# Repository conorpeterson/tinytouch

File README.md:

# TinyTouch
** Simple and reliable finger-to-PCB touch sensing **   
By Conor Peterson - conor.p.peterson@gmail.com 2016

License: Creative Commons Attribution-ShareAlike 4.0 International (CC BY-SA 4.0)

This project demonstrates simple and reliable on/off capacitive touch sensing. It is designed for use in interactive artworks or museum displays but would be well-suited for any hardwired application that requires oversized, physically accessible buttons located a distance from the controlling hardware.

The project is built around an ATtiny microcontroller so is compatible with 5v and 3.3v power supplies. The output of the detection unit is a clean high/low signal. Presses of variable duration are detected within reasonable limits.

The sensing element is built into the PCB itself and is designed to be directly touched by the user for maximum reliability. Material may be placed over the sensing element but should be kept thin, no thicker than typing paper (~.003" / .08mm). Certain materials may require adjustment of sensitivity threshold, or more substantial adaptations including the sensing element resistors (R3 and R4), the sampling interval or possibly the clock speed of the microcontroller.

One of the challenges in capacitive touch sensing is that the measurements tend to drift according to changes in temperature and humidity. This design attempts to address this by calibrating the detection floor at startup and at regular intervals thereafter. Consequently the sensor is best suited for momentary presses only - continuous contact for more than several seconds is to be avoided.

## Contents
### Firmware
This folder contains the source code for the ATtiny25/45/85 microcontroller. It has been tested to compile within a Linux environment using avr-gcc 4.9.2 and avr-libc 1.8.0. The bin subfolder contains pre-compiled hex files suitable for flashing with avrdude. NOTE: you must alter the fuse bits so that the chip runs at 8 MHz; this can be done by invoking the "fuses" target in the supplied makefile.

### Schematic
Contains a Kicad 4.x schematic for the project, plus a the reference PCB layout and fabrication-ready gerbers. The artwork in the TT_SMT_GRAPHICS subfolder can be modified and passed through Kicad's bitmap-to-component converter to create the custom touch sensor soldermask.

## License
The contents of this project are provided under the Creative Commons Attribution-ShareAlike 4.0 license.
(https://creativecommons.org/licenses/by-sa/4.0/legalcode)

You are free to:  
Share — copy and redistribute the material in any medium or format  
Adapt — remix, transform, and build upon the material for any purpose, even commercially.  
Under the following terms:  
Attribution — You must give appropriate credit, provide a link to the license, and indicate if changes were made. You may do so in any reasonable manner, but not in any way that suggests the licensor endorses you or your use.  
ShareAlike — If you remix, transform, or build upon the material, you must distribute your contributions under the same license as the original.

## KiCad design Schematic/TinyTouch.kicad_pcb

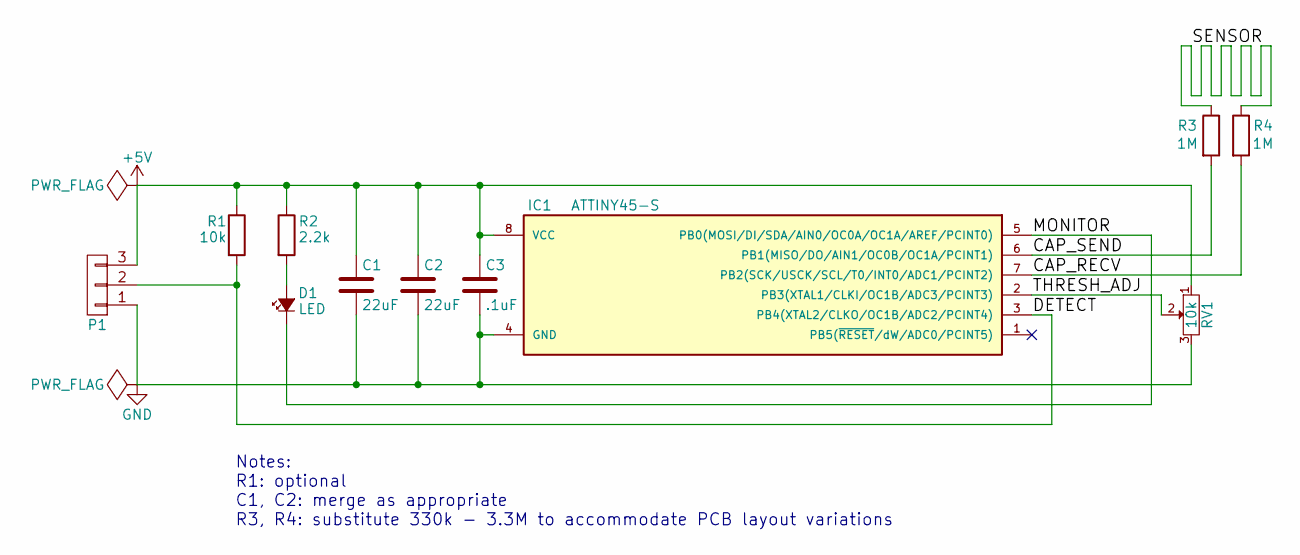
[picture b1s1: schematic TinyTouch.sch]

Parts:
C1, C2: 22uF; C_0805_HandSoldering
C3: .1uF; C_0805_HandSoldering
D1: LED; LED_0805_HandSoldering
IC1: ATTINY45-S; SOIJ-8_5.3x5.3mm_Pitch1.27mm
P1: CONN_01X03; CONN_1x3_DIRECTSOLDER
R1: 10k; R_0805_HandSoldering
R2: 2.2k; R_0805_HandSoldering
R3, R4: 1M; R_0805_HandSoldering
RV1: 10k; Bourns_SMD_Trimmer

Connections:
+5V: C1.1, C2.1, C3.1, IC1.8 (VCC), P1.3, R1.1, R2.1, RV1.1
/CAP_RECV: IC1.7 (PB2(SCK/USCK/SCL/T0/INT0/ADC1/PCINT2)), R4.2
/CAP_SEND: IC1.6 (PB1(MISO/DO/AIN1/OC0B/OC1A/PCINT1)), R3.2
/DETECT: IC1.3 (PB4(XTAL2/CLKO/OC1B/ADC2/PCINT4)), P1.2, R1.2
/MONITOR: D1.1 (K), IC1.5 (PB0(MOSI/DI/SDA/AIN0/OC0A/OC1A/AREF/PCI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)
/SENSOR: R3.1, R4.1
/THRESH_ADJ: IC1.2 (PB3(XTAL1/CLKI/OC1B/ADC3/PCINT3)), RV1.2
GND: C1.2, C2.2, C3.2, IC1.4 (GND), P1.1, RV1.3
unnamed: D1.2 (A), R2.2

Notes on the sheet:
Notes: R1: optional C1, C2: merge as appropriate R3, R4: substitute 330k - 3.3M to accommodate PCB layout variations

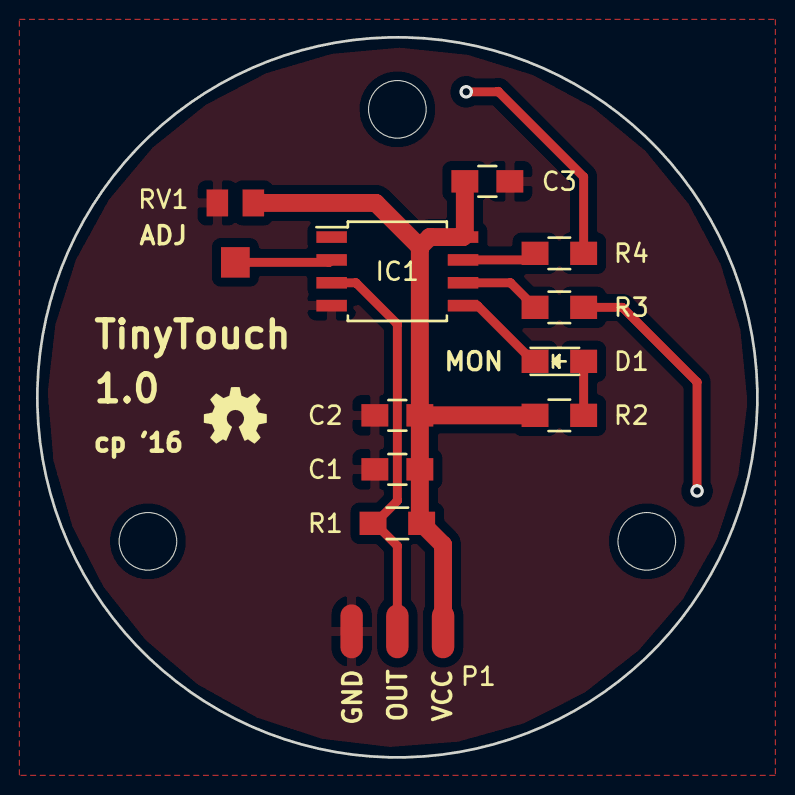
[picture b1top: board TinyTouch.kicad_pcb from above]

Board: 2 copper layers, 40.0 x 40.0 mm, 15 parts (1 on the bottom side), 9 nets.

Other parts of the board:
SCREW_1, SCREW_2, SCREW_3: MountingHole_3.2mm_M3_ISO7380
SENS: LOGO; cap_touch_40mm

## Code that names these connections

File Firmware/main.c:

/*
 * TinyTouch - main.c
 * (C) 2016 Conor Peterson
 * conor.p.peterson@gmail.com
 * http://www.conorpeterson.org
 * 
 * This software is licensed to you under the terms of the 
 * Creative Commons Attribution ShareAlike 4.0 International license
 * (CC BY-SA 4.0). See also https://creativecommons.org/licenses/by-sa/4.0/
 * 
 * You are free to share and adapt this software for any purpose, even commercially,
 * so long as you attribute the original author, and distribute your modifications
 * under the same license as the original.
 * 
 * 
 * This firmware runs on the TinyTouch, monitoring a capacitive touch sensor and
 * relaying the status via the DETECT line. The threshold is set via potentiometer
 * connected to ADC3 (PB4). Status of the sensor and detection is output on PB3
 * via PWM. Noise floor is adjusted automatically.
 * 
 * This firmware will run on any from the ATtiny25/45/85 line.
 * 
 */

#include <avr/io.h>
#include <util/delay.h>
#include <avr/interrupt.h>

//Major adjustments
#define WINDOW_LEN 8 //Store the last x readings for calculating touches. Power of 2.
#define NF_PERIOD 16 //Every NF_PERIOD samples, adjust the noise floor.

//Pin definitions - ATtiny25/45/85.
#define B_CAP_RECV	PB2
#define B_CAP_SEND	PB1
#define B_DETECT	PB4 //Externally pulled high, but driven normally
#define B_THRESH	PB3 //Set thresh via ADC3
#define B_MONITOR	PB0 //PWM visualizing via OC0A. Inverted logic.

//Port manipulation macros
#define SBI(port, pin) (port) |=  (1 << (pin))
#define CBI(port, pin) (port) &= ~(1 << (pin))

//Function definitions
void loop(void);
int main(void);
void adjust_threshold(void);
uint16_t sample(void);
int16_t sum_samples(void);
uint16_t sense(void);
ISR(TIMER1_COMPA_vect);
uint8_t analog_read(void);

//Global variables
int16_t noisefloor = 0;
uint8_t noisefloor_counter = NF_PERIOD;
int16_t samples[WINDOW_LEN];
uint8_t sample_cursor = 0;
uint8_t threshold = 3 * WINDOW_LEN;
volatile uint8_t event = 0;

//Interrupt on Timer1 OCIE1A controls the frequency of the sampling routine.
ISR(TIMER1_COMPA_vect)
{
	event = 1;
}

int main(void)
{
	cli(); //Disable interrupts
	
	//Timer1 is used for setting the sampling period.
	TCCR1 = _BV(CS13) | _BV(CS11) | _BV(CS10); //Prescale = /1024
	TCCR1 |= _BV(CTC1); //Clear timer on compare match C (freq. adj. via OCR1C)
	TIMSK = _BV(OCIE1A); //Interrupt on compare match A
	OCR1A = 0; //Request interrupt when TNCT1 rolls over to zero
	OCR1C = 161; //OCR1C adjusts of Timer1 -- NOTE approximately what frequency is this, 50Hz?
	
	//Timer0 is used for visualizing the state of the sensor via PWM-faded LED
	TCCR0A = _BV(WGM01) | _BV(WGM00); //Fast PWM mode with TOP as 0xFF (adjustable duty cycle mode)
	TCCR0A |= _BV(COM0A1) | _BV(COM0A0); //Set OC0A at compare match, clear OC0A at bottom (inverting mode)
	TCCR0B = _BV(CS01) | _BV(CS00); //Prescale /64
	OCR0A = 128; //Almost immediately overridden, but can help catch early hangs
	SBI(DDRB, B_MONITOR); //B_MONITOR as an output
	
	//ADC3 is used to adjust the sensitivity
	ADMUX = _BV(MUX1) | _BV(MUX0); //ADC3 (PB3 or pin 2)
	ADMUX |= _BV(ADLAR); //Left-adjusted results (8-bit mode)
	ADCSRA = _BV(ADEN); //Enable ADC
	ADCSRA |= _BV(ADPS1) | _BV(ADPS0); //ADC clock prescaled by /8
	DIDR0 = _BV(ADC3D); //Disable digital IO on ADC3 to save power
	
	//Pin configuration
	SBI(DDRB, B_DETECT); //B_DETECT as output
	CBI(PORTB, B_DETECT); //B_DETECT driven low
	
	//Establish baselines for the noisefloor and trigger threshold
	noisefloor = sample();
	adjust_threshold();
	
	sei();	//Enable interrupts
	
	for(;;) {
		loop();
	}

	return 0; //Never reached
}

void loop(void)
{
	int16_t reading;
	int16_t area;

	while( !event ) {};
	event = 0;
	
	reading = sample();
	
	if( ++noisefloor_counter >= NF_PERIOD ) {
		noisefloor_counter = 0;
		if( reading != noisefloor ) {
			noisefloor += (reading > noisefloor) ? 1 : -1;
		}
		
		//Occasionally sample ADC3 and adjust the threshold
		adjust_threshold();
	}
	
	reading -= noisefloor;
	
	samples[sample_cursor++] = reading;
	sample_cursor &= WINDOW_LEN;

	area = sum_samples();

	if( area > 0 ) {
		if( area > 255 || area > threshold ) {
			OCR0A = 255;
		} else {
			OCR0A = area; //Update monitor
		}
	} else {
		OCR0A = 0;
	}

    if( area > threshold ) {
		SBI(PORTB, B_DETECT); //B_DETECT driven HIGH
	} else {
		CBI(PORTB, B_DETECT); //B_DETECT driven LOW
	}
}

uint8_t analog_read(void)
{
	SBI(ADCSRA, ADSC); //Start conversion
	while( ADCSRA & _BV(ADSC) ) {}; //Wait for conversion to end
	return ADCH;
}

//Whenever a new sample is logged, it and several preceeding samples are summed and
//compared to threshold. I ran several experiments and found a useful range between 
//8 (WINDOW_LEN * 1) and 64 (WINDOW_LEN * 8), with a good compromise at 24 (WINDOW_LEN * 3).
//The threshold is adjusted by setting an analog pot, which is sampled and remapped every
//few sensing intervals.
void adjust_threshold(void)
{
	uint8_t value;
	value = analog_read();
	threshold = value;
}

//4X oversampling to reduce noise
uint16_t sample(void)
{
	uint32_t accum = 0;
	accum = sense();
	accum += sense();
	accum += sense();
	accum += sense();
	accum >>= 2;
	return (uint16_t)accum;
}

int16_t sum_samples(void)
{
	uint8_t i;
	int16_t accum = 0;
	for(i = 0; i < WINDOW_LEN; i++) {
		accum += samples[i];
	}
	return accum;
}

uint16_t sense(void)
{
	uint16_t counter = 0;
	
	//Totally discharge the sensor
	SBI(DDRB, B_CAP_SEND);  //Send as output
	SBI(DDRB, B_CAP_RECV);  //Receive as output

	CBI(PORTB, B_CAP_SEND); //Drive send LOW
	CBI(PORTB, B_CAP_RECV); //Drive receive LOW
	_delay_us(50); //wait...

	//Charge the sensor and watch the rise time.
	CBI(DDRB, B_CAP_RECV); //Recv now an input
	cli(); //Disable interrupts
	SBI(PORTB, B_CAP_SEND); //Drive send HIGH
	while( (PINB & _BV(B_CAP_RECV)) == 0  ) {
		counter++;
		//Catch timeouts - testing against zero appears free in assembled output.
		if( counter == 0 ) {
			break;
		}
	}
	sei(); //Re-enable interrupts
	//Finish the charge to VCC
	SBI(PORTB, B_CAP_RECV); //Recv pull-up on
	SBI(DDRB, B_CAP_RECV); //Recv as output
	_delay_us(50);
	CBI(DDRB, B_CAP_RECV); //Recv as input
	CBI(PORTB, B_CAP_RECV); //Recv floating
	cli(); //Disable interrupts
	CBI(PORTB, B_CAP_SEND); //Drive send LOW
	while( (PINB & _BV(B_CAP_RECV)) != 0 ) {
		counter++;
		if( counter == 0 ) {
			break;
		}
	}
	sei(); //Re-enable interrupts
	return counter;
}

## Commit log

2016-11-26 markdown adjustments
2017-01-20 Added scans of the PCB itself
2017-02-05 More conservative fuses in Makefile
2017-05-16 Markdown error
